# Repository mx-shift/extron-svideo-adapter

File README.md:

# Extron S-Video Adapter

A small, passive breakout board for connecting an S-video source and stereo
analog audio to an Extron IN1606 scaling presentation switcher.

The IN1606's two analog video inputs use 15-pin HD (VGA-style) connectors. They
accept S-video, but there's no 4-pin Mini-DIN jack to plug a source into. This
board routes a standard S-video Mini-DIN onto the HD-15 pins the IN1606 expects
for S-video. It also breaks out stereo audio between RCA jacks and a 3.5 mm
5-position pluggable header.

J1 is a female HD-15, like the IN1606's inputs, so connect the two with a
male-to-male HD-15 (VGA) cable. A cable with all 15 conductors isn't needed;
pins 2, 3, 7, 8 and 10 must be connected.

## Specifications

- 2-layer, 1.6 mm FR-4, 43.18 × 63.5 mm
- All through-hole parts; no active components
- Designed in KiCad 10

## Connectors

| Ref | Function             | Part |
|-----|----------------------|------|
| J1  | HD-15 to IN1606      | [Amphenol L77HDE15SD1CH4F](https://www.amphenol-cs.com/product/l77hde15sd1ch4f.html) |
| J2  | S-video (Mini-DIN 4) | [TE Connectivity 5749181-1](https://www.te.com/en/product-5749181-1.html) |
| J3  | Audio header         | [TE Connectivity 284512-5](https://www.te.com/en/product-284512-5.html) (3.5 mm, 5-pos) |
| J4  | Audio RCA (L/R)      | [Same Sky (formerly CUI Devices) RCJ-2123](https://www.sameskydevices.com/product/interconnect/audio-connectors/rca-jacks/rcj-21) |

The HD-15 and audio wiring follow the "Analog Video Connection" pinout table
and "Analog Audio Connection" figure in the IN1606/IN1608 user guide (Extron
document 68-2290-01), available from the
[IN1606 product page](https://www.extron.com/product/in1606).

## Pinout

### Video

| Signal        | J2 (Mini-DIN) | J1 (HD-15) |
|---------------|:-------------:|:----------:|
| Luma (Y)      | 3             | 2          |
| Luma return   | 1             | 7          |
| Chroma (C)    | 4             | 3          |
| Chroma return | 2             | 8          |
| Ground        | shell         | 10, shell  |

All other HD-15 pins are unconnected.

### Audio

| Signal       | J4 (RCA) | J3 (header)         |
|--------------|:--------:|:-------------------:|
| Left         | 4        | 1                   |
| Right        | 2        | 4                   |
| Audio ground | 1, 3     | 2, 3, 5             |

Audio ground is kept separate from the video/chassis ground.

J3 is a pluggable header with the same 3.5 mm 5-position format as the
IN1606's audio inputs. Make the audio cable with a
[TE 284506-5](https://www.te.com/en/product-284506-5.html) screw-terminal plug
at each end, wired pin-for-pin (L+, L−, ⏚, R+, R−). This matches Extron's
unbalanced input wiring.

## Revision history

- **Rev 2:** Fixed the S-video jack (J2) footprint, whose signal pins were
  mirrored left-to-right, and rerouted the video traces. Also plated the RCA
  mounting-tab slots, adjusted pad and drill sizes, added silkscreen labels,
  and set design rules for OSH Park's 2-layer service.
- **Rev 1:** Original fabricated board. J2's pinout is reversed; installing
  the jack on the bottom side of the board corrects it.

## Ordering boards

Download `extron-svideo-adapter-<version>-oshpark.zip` from the
[latest release](https://github.com/mx-shift/extron-svideo-adapter/releases/latest)
(or the `outputs` artifact of any Actions run). It contains the Gerbers and
the Excellon drill file. Upload the zip to [OSH Park](https://oshpark.com/).
The board is designed to OSH Park's 2-layer rules. Use the zip rather than the
`.kicad_pcb` file: the design is in KiCad 10 format, and OSH Park processes
uploaded board files with an older KiCad.

The release's `-bom.csv` lists the parts that solder to the board and imports
into DigiKey's BOM Manager. You'll also need:

- 2 × [TE Connectivity 284506-5](https://www.te.com/en/product-284506-5.html)
  3.5 mm 5-position screw-terminal plugs for the audio cable: one mates with
  J3 and the other with the IN1606's audio input. You can use the IN1606's own
  captive-screw plug for its end instead.
- 1 × male-to-male HD-15 (VGA) cable to connect J1 to the IN1606

## Case

`case/case.scad` is a two-part, 3D-printable case. The bottom shell holds the
board on ledges along its two connector-free edges, and walls inside the top
shell clamp the same strips from above. The top shell's side walls have
openings for the connectors. Ears on the bottom shell let you screw the case
to a surface. Assembled, it measures 47.8 × 84.1 × 31.1 mm (104 mm long
including the ears).

STLs for both shells are attached to each
[release](https://github.com/mx-shift/extron-svideo-adapter/releases/latest)
and to every Actions run (the `case` artifact), already oriented for printing.

Hardware:

- 4 × M3 × 25 socket head cap screws
- 4 × M3 heat-set inserts for 4.0 mm holes, at least 5 mm long (set
  `insert_d` to about 2.6 to self-tap the screws instead)
- 4 × #8 or M4 screws to mount the case (4.5 mm holes)

Printing: PLA or PETG, 0.2 mm layers, no supports. Print the bottom shell
floor-down and the top shell roof-down, as exported.

Assembly: install the inserts in the bottom shell, drop the board in, lower
the top shell over the connectors, and fit the screws.

The connector openings are sized from the manufacturers' drawings. The
`check` part in `case.scad` verifies that the case doesn't intersect the board
or the connector bodies. Mating plugs with oversized bodies or overmolds may
stop against the walls before fully seating: the S-video opening is
14.9 × 13.4 mm, the RCA slots are 11 mm wide, and the audio plug opening is
21.7 × 14 mm. The audio plug opening was not checked against the mating
plug's drawing. Adjust the parameters at the top of `case.scad` if needed.

## Building

`scripts/build.sh` runs ERC and DRC, then writes the schematic PDF, a BOM CSV
that imports into DigiKey's BOM Manager, and the OSH Park package to
`output/`. GitHub Actions runs it in the `kicad/kicad`
container on every push and pull request; pushing a `v*` tag also publishes a
release with the zip, schematic PDF, BOM, and case STLs. To run it locally:

```sh
scripts/build.sh
# or, with the KiCad Flatpak:
KICAD_CLI="flatpak run --command=kicad-cli org.kicad.KiCad" scripts/build.sh
```

`scripts/build-case.sh` runs the case collision check and exports the STLs to
`output-case/`. It needs OpenSCAD.

The source location printed on the board and in the title blocks is the
`SOURCE_URL` project text variable (Schematic/Board Setup → Text Variables).

## Repository layout

- `extron-svideo-adapter.kicad_pro`, `.kicad_sch`, `.kicad_pcb`: KiCad project
- `extron-svideo-adapter.pretty/`: custom footprints for the connectors above.
  The project library table (`fp-lib-table`) loads them automatically.
- `case/case.scad`: 3D-printable case (OpenSCAD)
- `scripts/build.sh`, `scripts/build-case.sh`, `.github/workflows/build.yml`:
  design checks, fabrication outputs, and case STLs

## License

Copyright Rick Altherr 2023-2026.

This hardware design is licensed under the CERN Open Hardware Licence
Version 2 - Strongly Reciprocal (SPDX: `CERN-OHL-S-2.0`). See
[LICENSE](LICENSE) for the full text.

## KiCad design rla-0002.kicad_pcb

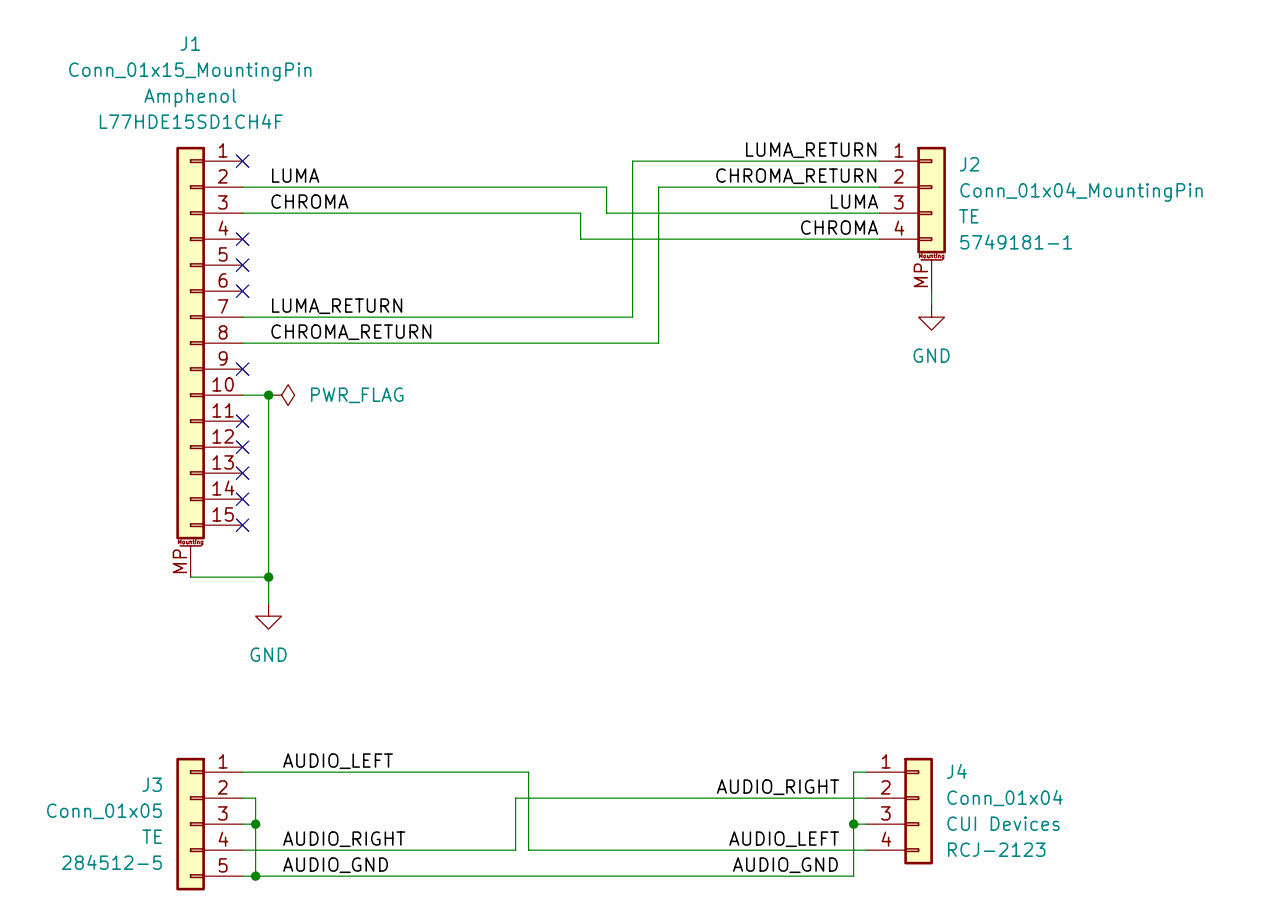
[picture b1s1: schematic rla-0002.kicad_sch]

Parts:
J1: Conn_01x15_MountingPin; DSUB-15-HD_Female_Horizontal_P2.29x2.54mm_EdgePinOffset8.89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; Manufacturer Part Number L77HDE15SD1CH4F
J2: Conn_01x04_MountingPin; MiniDIN_4_Female_Horizontal_P6.7x2.5mm_THT; Manufacturer Part Number 5749181-1
J3: Conn_01x05; TerminalBlock_TE_284512-5_1x05_P3.5mm_Horizontal; Manufacturer Part Number 284512-5
J4: Conn_01x04; Jack_RCA_1x2_CUI_RCJ-21XX_Horizontal_THT; Manufacturer Part Number RCJ-2123

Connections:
/AUDIO_GND: J3.2, J3.3, J3.5, J4.1, J4.3
/AUDIO_LEFT: J3.1, J4.4
/AUDIO_RIGHT: J3.4, J4.2
/CHROMA: J1.3, J2.4
/CHROMA_RETURN: J1.8, J2.2
/LUMA: J1.2, J2.3
/LUMA_RETURN: J1.7, J2.1
GND: J1.10, J1.MP (MountPin), J2.MP (MountPin)

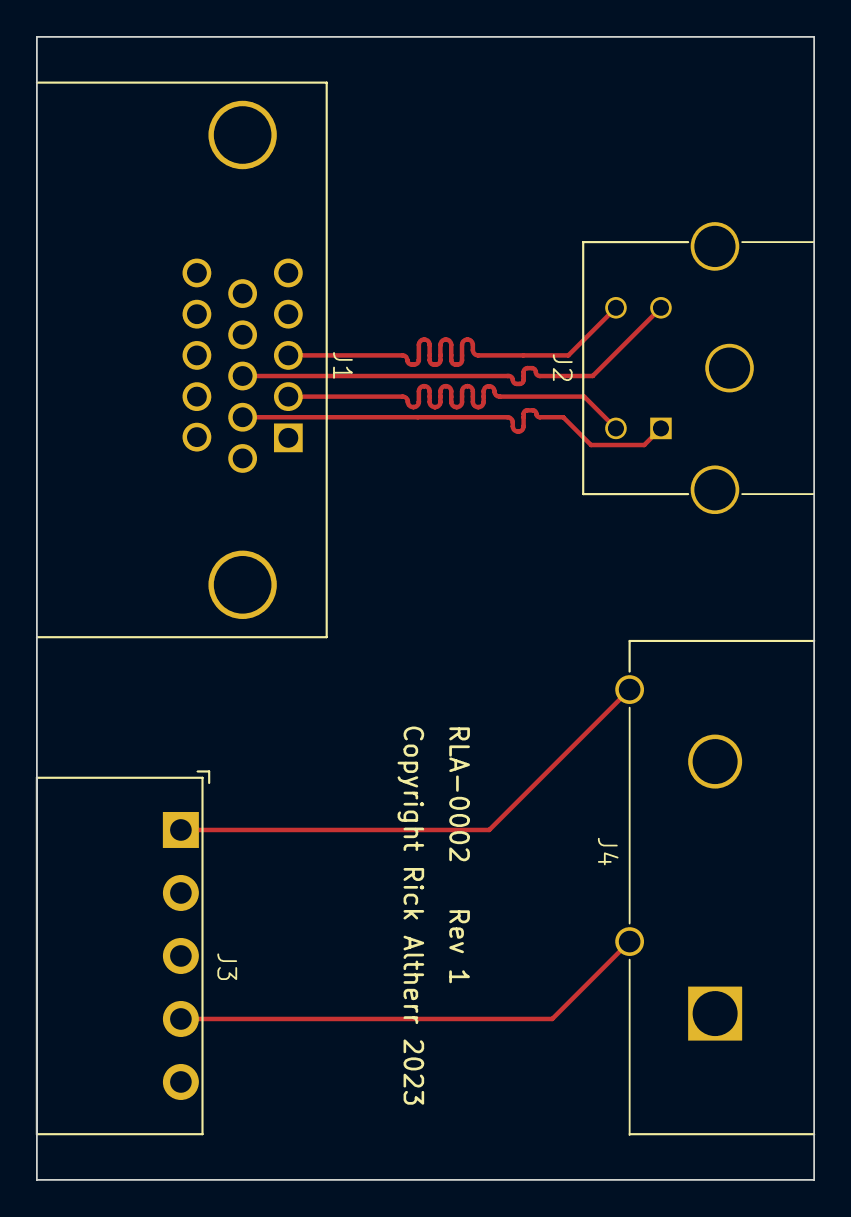
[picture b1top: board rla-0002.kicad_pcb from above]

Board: 2 copper layers, 43.2 x 63.5 mm, 4 parts (0 on the bottom side), 8 nets.

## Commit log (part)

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2023-07-28 Add README
2023-09-04 initial schematic and audio terminal block footprint
2023-09-17 Change video in connector to Amphenol L77HDE15SD1CH4F
2023-09-17 Change audio input connector to TE 284512-5
2023-09-17 Footprint for DSUB-15HD compatible with Amphenol L77HDE15SD1CH4F
2023-09-17 Ignore fp-info-cache as it will be rebuilt by KiCAD as necessary
2023-09-17 Pin rla-0002 footprint library to top of library list
2023-09-17 Change video out connector to TE 5749181-1
2023-09-17 Footprint for 4-pin Mini-DIN compatible with TE 5749181-1
2023-09-17 Footprint for CUI RCJ-21XX dual RCA jack
2023-09-17 Change audio out connector to CUI RCJ-2123
2023-09-17 Connect connector mounting holes to DDC ground
2023-09-17 Move TerminalBlock_TE_284512-5_1x05_P3.5mm_Horizontal pin 1 indicator to more sensible location
2023-09-17 Fix incorrect pad placement on MiniDIN_4_Female_Horizontal_P6.7x2.49mm_THT
2023-09-17 Fix name of MiniDIN_4_Female_Horizontal_P6.7x2.49mm_THT to reflect correct pitch of 6.7x2.5mm
